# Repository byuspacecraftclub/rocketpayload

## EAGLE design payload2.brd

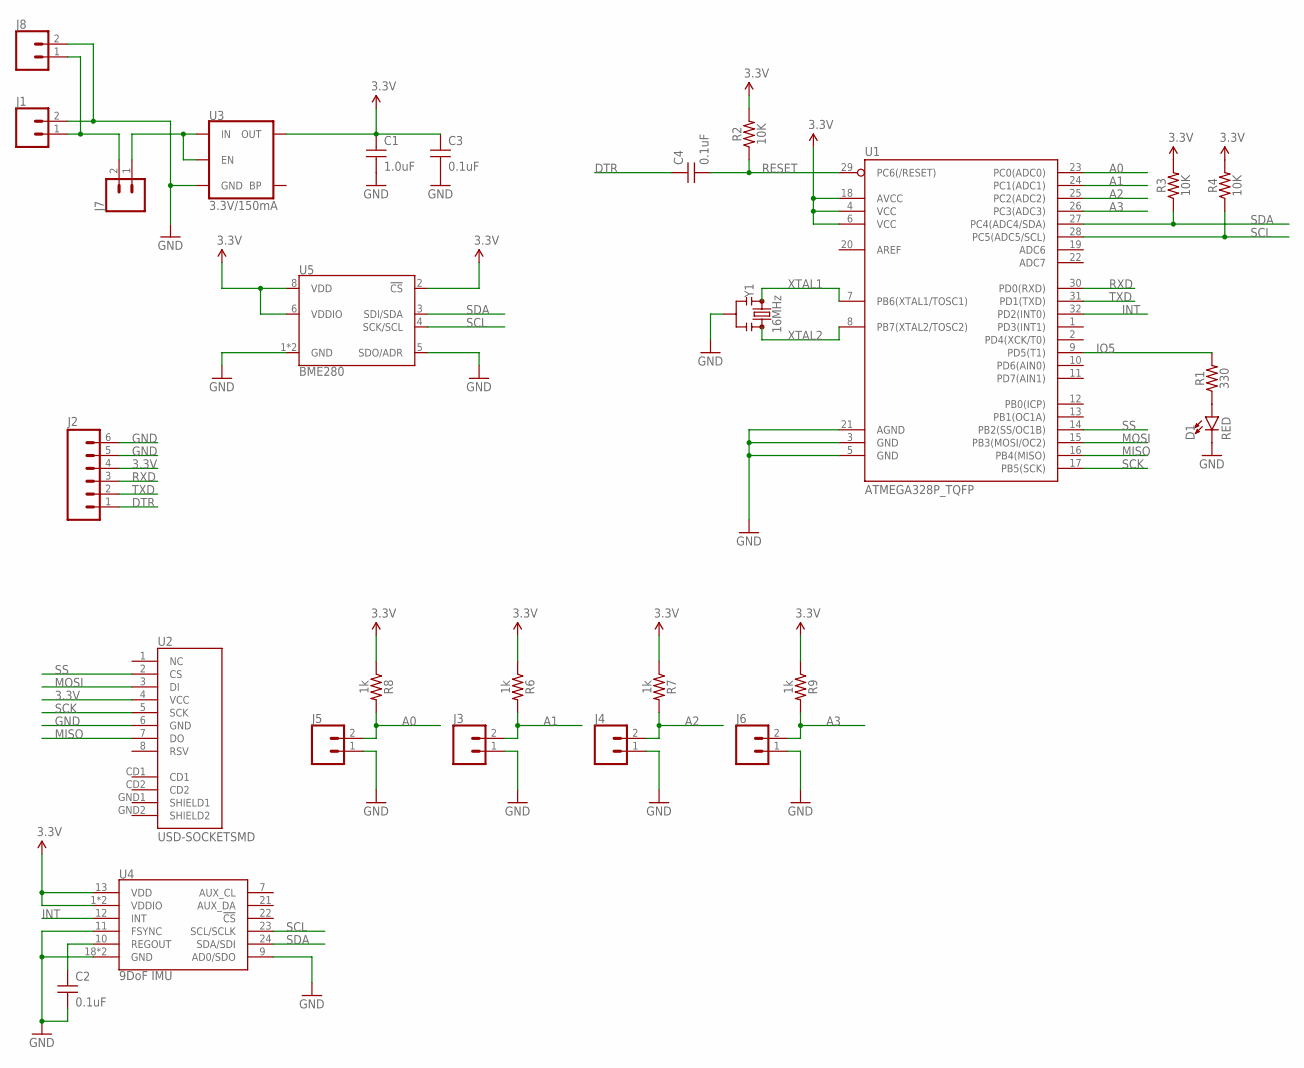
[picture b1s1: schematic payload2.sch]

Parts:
C1: 1.0uF; 0603
C2, C3, C4: 0.1uF; 0603-CAP
D1: RED; LED-0603
J1, J3, J4, J5, J6, J7, J8: CONN_02; 1X02
J2: CONNECTOR_6PINSILK_FEMALE_PTH; 1X06
R1: 330; 0603
R2, R3, R4: 10K; 0603-RES
R6, R7, R8, R9: 1k; 0603
U1: ATMEGA328P_TQFP; TQFP32-08
U2: USD-SOCKETSMD; MICRO-SD-SOCKET-PP
U3: 3.3V/150mA; SOT23-5
U4: 9DoF IMU; QFN24-3X3
U5: BME280; LGA-8-2.5X2.5
Y1: 16MHz; RESONATOR-SMD-3.2X1.3

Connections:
3.3V: C1.1, C3.1, J2.4, R2.2, R3.2, R4.2, R6.1, R7.1, R8.1, R9.1, U1.4 (VCC), U1.6 (VCC), U1.18 (AVCC), U2.4 (VCC), U3.5 (OUT), U4.1 (VDDIO), U4.8 (VDDIO), U4.13 (VDD), U5.2 (!CS), U5.6 (VDDIO), U5.8 (VDD)
A0: J5.2, R8.2, U1.23 (PC0(ADC0))
A1: J3.2, R6.2, U1.24 (PC1(ADC1))
A2: J4.2, R7.2, U1.25 (PC2(ADC2))
A3: J6.2, R9.2, U1.26 (PC3(ADC3))
DTR: C4.1, J2.1
GND: C1.2, C2.2, C3.2, D1.C, J1.2, J2.5, J2.6, J3.1, J4.1, J5.1, J6.1, J8.2, U1.3 (GND), U1.5 (GND), U1.21 (AGND), U2.6 (GND), U3.2 (GND), U4.9 (AD0/SDO), U4.11 (FSYNC), U4.18 (GND), U4.20 (GND), U5.1 (GND), U5.5 (SDO/ADR), U5.7 (GND), Y1.2
INT: U1.32 (PD2(INT0)), U4.12 (INT)
IO5: R1.2, U1.9 (PD5(T1))
MISO: U1.16 (PB4(MISO)), U2.7 (DO)
MOSI: U1.15 (PB3(MOSI/OC2)), U2.3 (DI)
unnamed: J7.1, U3.1 (IN), U3.3 (EN)
unnamed: D1.A, R1.1
unnamed: C2.1, U4.10 (REGOUT)
RESET: C4.2, R2.1, U1.29 (PC6(/RESET))
RXD: J2.3, U1.30 (PD0(RXD))
SCK: U1.17 (PB5(SCK)), U2.5 (SCK)
SCL: R4.1, U1.28 (PC5(ADC5/SCL)), U4.23 (SCL/SCLK), U5.4 (SCK/SCL)
SDA: R3.1, U1.27 (PC4(ADC4/SDA)), U4.24 (SDA/SDI), U5.3 (SDI/SDA)
SS: U1.14 (PB2(SS/OC1B)), U2.2 (CS)
TXD: J2.2, U1.31 (PD1(TXD))
VIN: J1.1, J7.2, J8.1
XTAL1: U1.7 (PB6(XTAL1/TOSC1)), Y1.1
XTAL2: U1.8 (PB7(XTAL2/TOSC2)), Y1.3

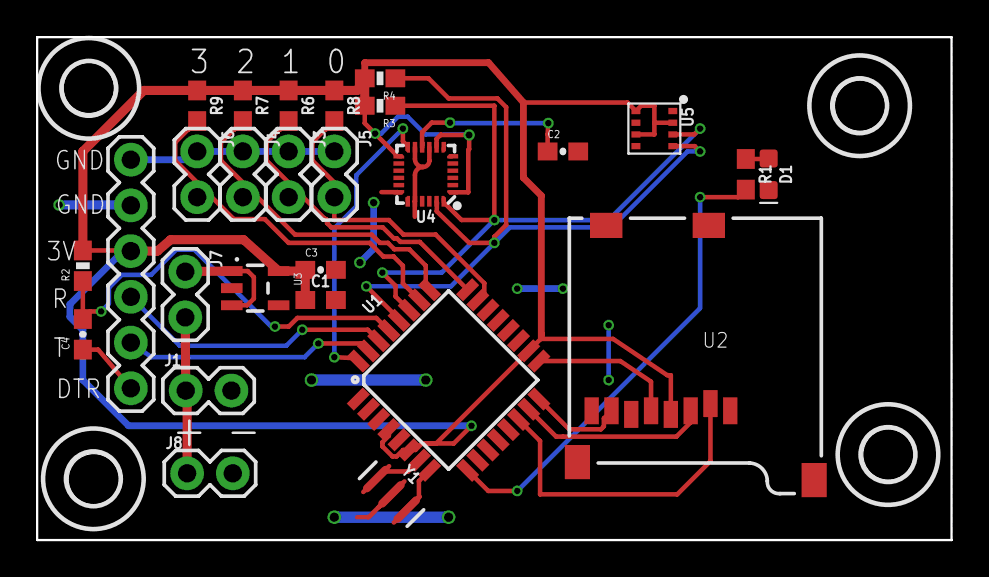
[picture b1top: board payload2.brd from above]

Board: 2 copper layers, 50.8 x 27.9 mm, 27 parts (0 on the bottom side), 24 nets.

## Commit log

2018-04-19 Initial commit of schematic and circuit board
2018-04-19 added connection to sd card
2018-04-19 This is the starting skeleton code that defines all of the functions for the project
2018-04-19 This is the code with some initialation functions and with the saving functions.
2018-04-19 add board file
2018-04-19 Started moving components in board file
2018-04-24 Worked on routing on board file. Added screw switch connectors.
2018-04-26 Finalized board design. Worked screw sizes and possitioning. Switched two hole connector for battery connector. added jumpers for battery charger.
    Board should be ready to order. Things that still need to improve:
    1) final check and look over.
    2) silk screen could be improved.
2018-04-26 This is just a couple of tiny tweaks that I added to Colby's design.
2018-04-26 Review of payload PCB complete
2018-04-28 Added to silkscreen arround programming header. Didn't change anything else.
2018-04-28 Tented vias.
2018-04-30 Added pressure sensor for gits and giggles.
2018-05-02 Added the IMU library I used to make the rocketPayload code in case someone else doesn't have the same version. It is comporised of the MPU9250 and quaternionFilters files. I'm not sure if I ever act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
2018-05-03 I made some minor bug fixes as well as put a lot of functionality into the interrupt code. Although the interrupt is working quite yet.
2018-05-16 The code now has sleeping functionality.
2018-05-17 testing
2018-05-17 temperature team code added
2018-06-11 payload code with all of the pieces working together.
2018-06-12 finished code? it hasn't been thoroughly tested, but it's all there.)
2018-06-12 miniscule changes
2018-06-14 final working code and temperature reading test
2018-06-16 launched code (and temp calibration test)

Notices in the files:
parts and their libraries:
SparkFun-Connectors: Licensing: Creative Commons ShareAlike 4.0 International - https://creativecommons.org/licenses/by-sa/4.0
